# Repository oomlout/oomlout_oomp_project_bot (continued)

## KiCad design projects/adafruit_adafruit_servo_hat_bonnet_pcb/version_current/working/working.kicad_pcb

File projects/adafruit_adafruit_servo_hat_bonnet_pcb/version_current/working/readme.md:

# OOMP Project  
## Adafruit-Servo-HAT-Bonnet-PCB  by adafruit  
  
oomp key: oomp_projects_flat_adafruit_adafruit_servo_hat_bonnet_pcb  
(snippet of original readme)  
  
- Adafruit-Servo-HAT-Bonnet-PCB  
PCB files for Adafruit Servo HAT and Bonnet  
  
Format is EagleCAD schematic and board layout  
  
For more details, check out the product pages at  
  
   * http://www.adafruit.com/product/2327  
   * https://www.adafruit.com/product/3416  
  
Adafruit invests time and resources providing this open source design,   
please support Adafruit and open-source hardware by purchasing   
products from Adafruit!  
  
Designed by Adafruit Industries.    
Creative Commons Attribution, Share-Alike license, check license.txt for more information  
All text above must be included in any redistribution  
  
  full source readme at [readme_src.md](readme_src.md)  
  
source repo at: [https://github.com/adafruit/Adafruit-Servo-HAT-Bonnet-PCB](https://github.com/adafruit/Adafruit-Servo-HAT-Bonnet-PCB)  
## Board  

## Schematic  

[schematic pdf](working_schematic.pdf)  
## Images

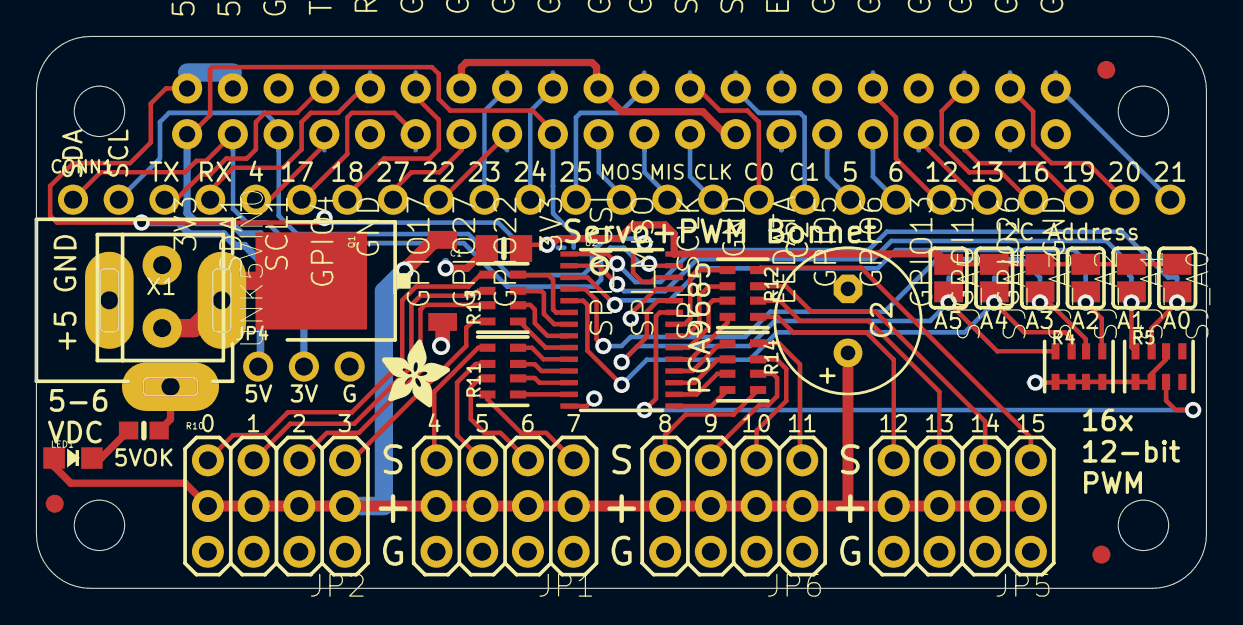
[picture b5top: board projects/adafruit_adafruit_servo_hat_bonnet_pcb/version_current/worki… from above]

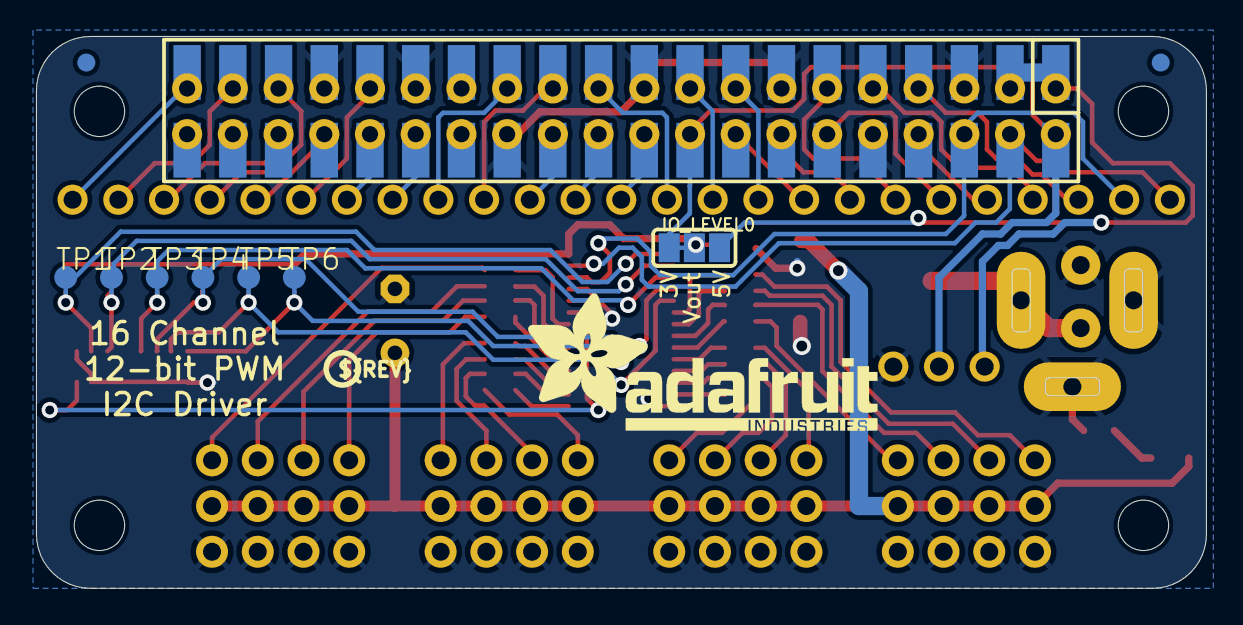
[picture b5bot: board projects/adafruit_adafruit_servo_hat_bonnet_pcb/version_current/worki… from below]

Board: 2 copper layers, 65.0 x 30.7 mm, 40 parts (9 on the bottom side), 74 nets.

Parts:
C1: 10uF; 0805-NO
C2: E3,5-8
CONN1: HEADER-1X25; 1X25_ROUND_70MIL
FID1, FID2, FID3: FIDUCIAL_1MM
IO_LEVEL0: SOLDERJUMPER_2WAY_OPEN_NOPASTE
JP1, JP2, JP5, JP6: 3X04
JP4: 1X03_ROUND
LED1: GREEN; CHIPLED_0805_NOOUTLINE
Q1: AOD417; TO252
R4, R5: 10K; RESPACK_4X0603
R10: 470; 0603-NO
R11, R12, R13, R14: 220; RESPACK_4X0603
RPI1: RASPBERRYPI_BPLUS_BONNET_THMSMT; PI_BONNET_THMSMT
SJ_A0, SJ_A1, SJ_A2, SJ_A3, SJ_A4, SJ_A5: SOLDERJUMPER_REFLOW_NOPASTE
TP1, TP2, TP3, TP4, TP5, TP6: TPB1,27; B1,27
U2: PCA9685; TSSOP28
U$6: ADAFRUIT_TEXT_20MM
U$8: ADAFRUIT_3.5MM
U$11: PCBFEAT-REV-040
UNK5VIN0: 3.5mm term; TERMBLOCK_1X2-3.5MM
X1: 2.1mm; DCJACK_2MM_PTH

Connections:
3.3V: IO_LEVEL0.1, JP4.2, RPI1.1, RPI1.17, RPI1.S1, RPI1.S17
5.0V: IO_LEVEL0.3, JP4.1, RPI1.2, RPI1.4, RPI1.S2, RPI1.S4
+5V: C2.+, JP1.2, JP1.5, JP1.8, JP1.11, JP2.2, JP2.5, JP2.8, JP2.11, JP5.2, JP5.5, JP5.8, JP5.11, JP6.2, JP6.5, JP6.8, JP6.11, LED1.A, Q1.2
A0: R5.7, SJ_A0.2, TP1.TP, U2.1
A1: R5.8, SJ_A1.2, TP2.TP, U2.2
A2: R4.5, SJ_A2.2, TP3.TP, U2.3
A3: R4.6, SJ_A3.2, TP4.TP, U2.4
A4: R4.7, SJ_A4.2, TP5.TP, U2.5
A5: R4.8, SJ_A5.2, TP6.TP, U2.24
EECLK: RPI1.28, RPI1.S28
EEDATA: RPI1.27, RPI1.S27
GND: C1.2, C2.-, JP1.3, JP1.6, JP1.9, JP1.12, JP2.3, JP2.6, JP2.9, JP2.12, JP4.3, JP5.3, JP5.6, JP5.9, JP5.12, JP6.3, JP6.6, JP6.9, JP6.12, Q1.1, R4.1, R4.2, R4.3, R4.4, R5.1, R5.2, R5.6, R10.2, RPI1.6, RPI1.9, RPI1.14, RPI1.20, RPI1.25, RPI1.30, RPI1.34, RPI1.39, RPI1.S6, RPI1.S9, RPI1.S14, RPI1.S20, RPI1.S25, RPI1.S30, RPI1.S34, RPI1.S39, U2.14, U2.25, UNK5VIN0.2, X1.GND, X1.GNDBREAK
GPIO4: CONN1.5, RPI1.7, RPI1.S7
GPIO5: CONN1.18, RPI1.29, RPI1.S29
GPIO6: CONN1.19, RPI1.31, RPI1.S31
GPIO12: CONN1.20, RPI1.32, RPI1.S32
GPIO13: CONN1.21, RPI1.33, RPI1.S33
GPIO16: CONN1.22, RPI1.36, RPI1.S36
GPIO17: CONN1.6, RPI1.11, RPI1.S11
GPIO18: CONN1.7, RPI1.12, RPI1.S12
GPIO19: CONN1.23, RPI1.35, RPI1.S35
GPIO20: CONN1.24, RPI1.38, RPI1.S38
GPIO21: CONN1.25, RPI1.40, RPI1.S40
GPIO22: CONN1.9, RPI1.15, RPI1.S15
GPIO23: CONN1.10, RPI1.16, RPI1.S16
GPIO24: CONN1.11, RPI1.18, RPI1.S18
GPIO25: CONN1.12, RPI1.22, RPI1.S22
GPIO26: RPI1.37, RPI1.S37
GPIO27: CONN1.8, RPI1.13, RPI1.S13
unnamed: LED1.C, R10.1
unnamed: JP1.4, R11.7
unnamed: JP1.1, R11.8
unnamed: JP1.7, R11.6
unnamed: JP1.10, R11.5
unnamed: JP2.1, R13.8
unnamed: JP2.4, R13.7
unnamed: JP2.7, R13.6
unnamed: JP2.10, R13.5
unnamed: JP6.10, R14.5
unnamed: JP6.7, R14.6
unnamed: JP6.4, R14.7
unnamed: JP6.1, R14.8
unnamed: JP5.10, R12.5
unnamed: JP5.7, R12.6
unnamed: JP5.4, R12.7
unnamed: JP5.1, R12.8
OE: R5.3, U2.23
PWM0: R13.4, U2.6
PWM1: R13.3, U2.7
PWM2: R13.2, U2.8
PWM3: R13.1, U2.9
PWM4: R11.4, U2.10
PWM5: R11.3, U2.11
PWM6: R11.2, U2.12
PWM7: R11.1, U2.13
PWM8: R14.4, U2.15
PWM9: R14.3, U2.16
PWM10: R14.2, U2.17
PWM11: R14.1, U2.18
PWM12: R12.4, U2.19
PWM13: R12.3, U2.20
PWM14: R12.2, U2.21
PWM15: R12.1, U2.22
PWR: Q1.3, UNK5VIN0.1, X1.PWR
RXD: CONN1.4, RPI1.10, RPI1.S10
SCL: CONN1.2, RPI1.5, RPI1.S5, U2.26
SDA: CONN1.1, RPI1.3, RPI1.S3, U2.27
SPI_CE0: CONN1.16, RPI1.24, RPI1.S24
SPI_CE1: CONN1.17, RPI1.26, RPI1.S26
SPI_MISO: CONN1.14, RPI1.21, RPI1.S21
SPI_MOSI: CONN1.13, RPI1.19, RPI1.S19
SPI_SCLK: CONN1.15, RPI1.23, RPI1.S23
TXD: CONN1.3, RPI1.8, RPI1.S8
VDDIO: C1.1, IO_LEVEL0.2, SJ_A0.1, SJ_A1.1, SJ_A2.1, SJ_A3.1, SJ_A4.1, SJ_A5.1, U2.28

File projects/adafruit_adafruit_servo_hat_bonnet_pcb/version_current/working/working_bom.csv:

"Id";"Designator";"Footprint";"Quantity";"Designation";"Supplier and ref";
1;"Q1";"TO252";1;"AOD417";;;
2;"JP5,JP2,JP1,JP6";"3X04";4;"";;;
3;"U$8";"ADAFRUIT_3.5MM";1;"";;;
4;"C1";"0805-NO";1;"10uF";;;
5;"JP4";"1X03_ROUND";1;"";;;
6;"FID3,FID2,FID1";"FIDUCIAL_1MM";3;"FIDUCIAL_1MM";;;
7;"R5,R4";"RESPACK_4X0603";2;"10K";;;
8;"U2";"TSSOP28";1;"PCA9685";;;
9;"RPI1";"PI_BONNET_THMSMT";1;"RASPBERRYPI_BPLUS_BONNET_THMSMT";;;
10;"R14,R11,R13,R12";"RESPACK_4X0603";4;"220";;;
11;"SJ_A3,SJ_A5,SJ_A4,SJ_A1,SJ_A0,SJ_A2";"SOLDERJUMPER_REFLOW_NOPASTE";6;"";;;
12;"CONN1";"1X25_ROUND_70MIL";1;"HEADER-1X25";;;
13;"C2";"E3,5-8";1;"";;;
14;"UNK5VIN0";"TERMBLOCK_1X2-3.5MM";1;"3.5mm term";;;
15;"X1";"DCJACK_2MM_PTH";1;"2.1mm";;;
16;"LED1";"CHIPLED_0805_NOOUTLINE";1;"GREEN";;;
17;"R10";"0603-NO";1;"470";;;
18;"TP5,TP2,TP1,TP3,TP4,TP6";"B1,27";6;"TPB1,27";;;
19;"U$6";"ADAFRUIT_TEXT_20MM";1;"";;;
20;"IO_LEVEL0";"SOLDERJUMPER_2WAY_OPEN_NOPASTE";1;"";;;
21;"U$11";"PCBFEAT-REV-040";1;"";;;

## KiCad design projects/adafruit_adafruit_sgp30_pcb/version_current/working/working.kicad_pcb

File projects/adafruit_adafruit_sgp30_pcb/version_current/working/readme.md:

# Adafruit-SGP30-PCB by adafruit  
This is a harvested standardized copy of a project from github.  
The original project can be found at:  
https://github.com/adafruit/Adafruit-SGP30-PCB  
Please consult that link for additional, details, files, and license information.  
Note: It was auto harvested and if the original repo had more than one board file or anything out of the ordinary the files here are likely not representative.

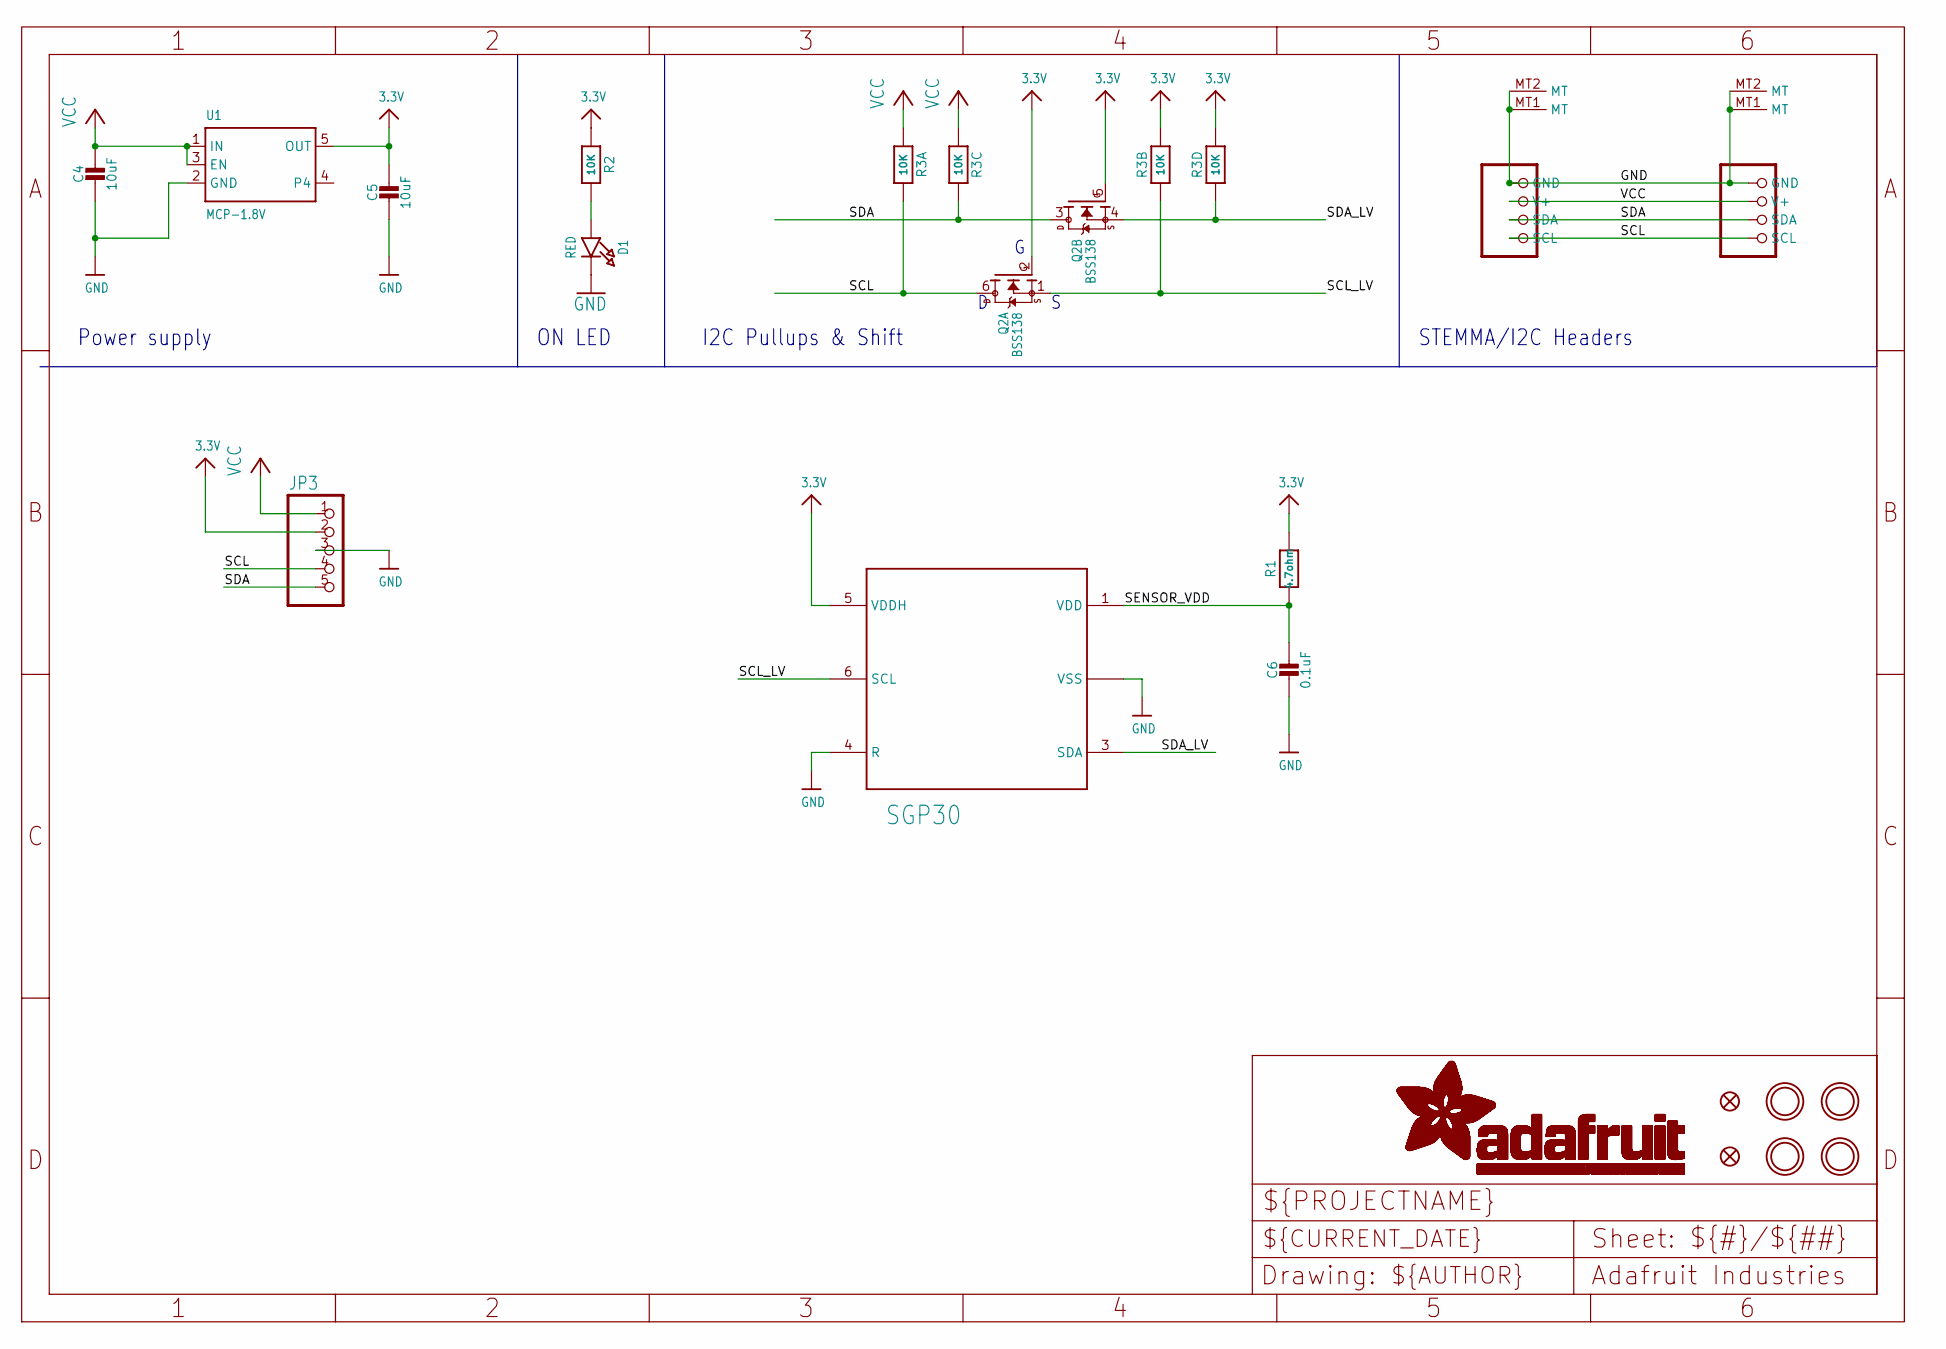
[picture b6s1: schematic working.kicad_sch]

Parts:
C4, C5: 10uF; 0805-NO
C6: 0.1uF; 0603-NO
CONN3, CONN4: STEMMA_I2C_QT; JST_SH4
D1: RED; CHIPLED_0603_NOOUTLINE
FID3, FID4: FIDUCIAL_1MM
JP3: HEADER-1X570MIL; 1X05_ROUND_70
Q2: BSS138; SOT363
R1: 4.7ohm; 0603-NO
R2: 10K; 0603-NO
R3: 10K; RESPACK_4X0603
U1: MCP-1.8V; SOT23-5
U$28, U$29, U$31, U$32: MOUNTINGHOLE2.5; MOUNTINGHOLE_2.5_PLATED
X1: SGP30

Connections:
3.3V: C5.1, JP3.2, Q2.2 (G), Q2.5 (G), R1.2, R2.1, R3.2 (1), R3.4 (1), U1.5 (OUT), X1.5 (VDDH)
GND: C4.2, C5.2, C6.2, CONN3.1 (GND), CONN3.MT1 (MT), CONN3.MT2 (MT), CONN4.1 (GND), CONN4.MT1 (MT), CONN4.MT2 (MT), D1.C, JP3.3, U1.2 (GND), X1.2 (VSS), X1.4 (R), X1.P$7 (VSS)
unnamed: D1.A, R2.2
SCL: CONN3.4 (SCL), CONN4.4 (SCL), JP3.4, Q2.6 (D), R3.8 (2)
SCL_LV: Q2.1 (S), R3.7 (2), X1.6 (SCL)
SDA: CONN3.3 (SDA), CONN4.3 (SDA), JP3.5, Q2.3 (D), R3.6 (2)
SDA_LV: Q2.4 (S), R3.5 (2), X1.3 (SDA)
SENSOR_VDD: C6.1, R1.1, X1.1 (VDD)
VCC: C4.1, CONN3.2 (V+), CONN4.2 (V+), JP3.1, R3.1, R3.3 (1), U1.1 (IN), U1.3 (EN)

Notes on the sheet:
ON LED
I2C Pullups & Shift
STEMMA/I2C Headers
Power supply

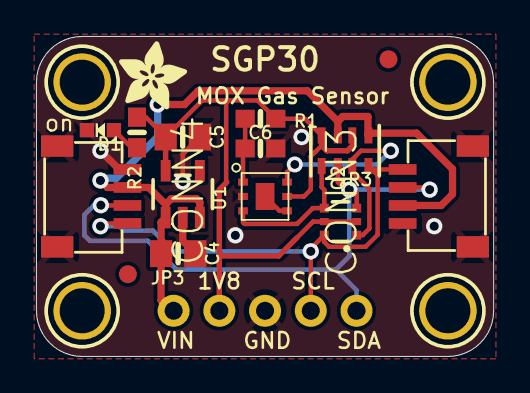
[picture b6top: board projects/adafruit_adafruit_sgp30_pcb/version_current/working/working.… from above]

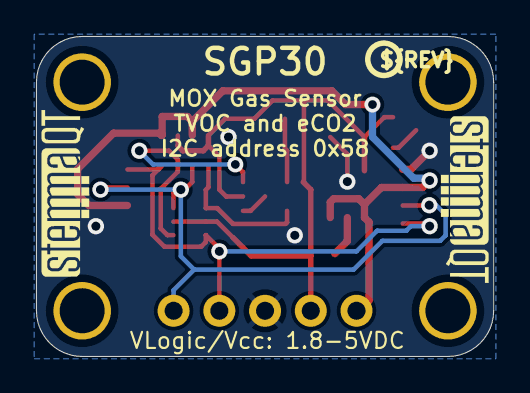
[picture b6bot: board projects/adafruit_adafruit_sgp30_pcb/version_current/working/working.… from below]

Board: 2 copper layers, 25.4 x 17.8 mm, 23 parts (3 on the bottom side), 9 nets.

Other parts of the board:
U$34: ADAFRUIT_3.5MM
U$35: PCBFEAT-REV-040
U$36, U$37: STEMMAQT

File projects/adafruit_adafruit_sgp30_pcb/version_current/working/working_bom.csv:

Row,Description,Part,References,Value,Footprint,Quantity Per PCB,Status,Datasheet
1,,CAP_CERAMIC0603_NO,C6,0.1uF,0603-NO,1, ,
2,,CAP_CERAMIC0805-NOOUTLINE,C4 C5,10uF,0805-NO,2, ,
3,,STEMMA_I2C_QT,CONN3 CONN4,STEMMA_I2C_QT,JST_SH4,2, ,
4,,LED0603_NOOUTLINE,D1,RED,CHIPLED_0603_NOOUTLINE,1, ,
5,,HEADER-1X570MIL,JP3,HEADER-1X570MIL,1X05_ROUND_70,1, ,
6,,MOSFET-N_DUAL,Q2,BSS138,SOT363,1, ,
7,,RESISTOR_0603_NOOUT,R1,4.7ohm,0603-NO,1, ,
8,,RESISTOR_0603_NOOUT,R2,10K,0603-NO,1, ,
9,,RESISTOR_4PACK,R3,10K,RESPACK_4X0603,1, ,
10,,VREG_SOT23-5,U1,MCP-1.8V,SOT23-5,1, ,
11,,SGP30,X1,SGP30,SGP30,1, ,





Project info:
Schematic:,working
Variant:,default
Revision:,
Date:,2023-08-03_17-21-23
KiCad Version:,7.0.6-7.0.6~ubuntu22.04.1
Statistics:
Component Groups:,11
Component Count:,13 (0 SMD/ 0 THT)
Fitted Components:,13 (0 SMD/ 0 THT)
Number of PCBs:,1
Total Components:,13

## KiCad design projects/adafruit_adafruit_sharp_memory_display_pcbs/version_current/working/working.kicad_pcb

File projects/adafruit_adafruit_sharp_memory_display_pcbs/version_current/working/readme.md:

# OOMP Project  
## Adafruit-Sharp-Memory-Display-PCBs  by adafruit  
  
oomp key: oomp_projects_flat_adafruit_adafruit_sharp_memory_display_pcbs  
(snippet of original readme)  
  
- PCB for the Adafruit Sharp Memory display breakout board  
  
<br />  

[The 96x96 resolution SHARP Memory LCD is no longer made, but we have a higher-resolution 168x144 display available in the shop](https://www.adafruit.com/product/3502).  
  
The 1.3" and 2.7" SHARP Memory LCD displays are a cross between an eInk (e-paper) display and an LCD. They have the ultra-low power usage of eInk and the fast-refresh rates of an LCD. This model has a matt silver background, and pixels show up as little mirrors for a silver-reflective display, a really beautiful and unique look. It does not have a backlight, but it is daylight readable. For dark/night reading you may need to illuminate the LCD area with external LEDs.  
  
The display is 3V powered and 3V logic, so we placed it on a fully assembled & tested breakout board with a 3V regulator and level shifting circuitry. The display slots into a ZIF socket on board and we use a piece of double-sided tape to adhere it onto one side. There are four mounting holes so you can easily attach it to a box.  
  
The display is 'write only' which means that it only needs 3 pins to send data. However, the downside of a write-only display is that the entire 96x96 bits (1,152 bytes) must be buffered by the microcontroller driver. On an Arduino Uno/Leonardo that  
  full source readme at [readme_src.md](readme_src.md)  
  
source repo at: [https://github.com/adafruit/Adafruit-Sharp-Memory-Display-PCBs](https://github.com/adafruit/Adafruit-Sharp-Memory-Display-PCBs)  
## Board  

## Schematic  

[schematic pdf](working_schematic.pdf)  
## Images

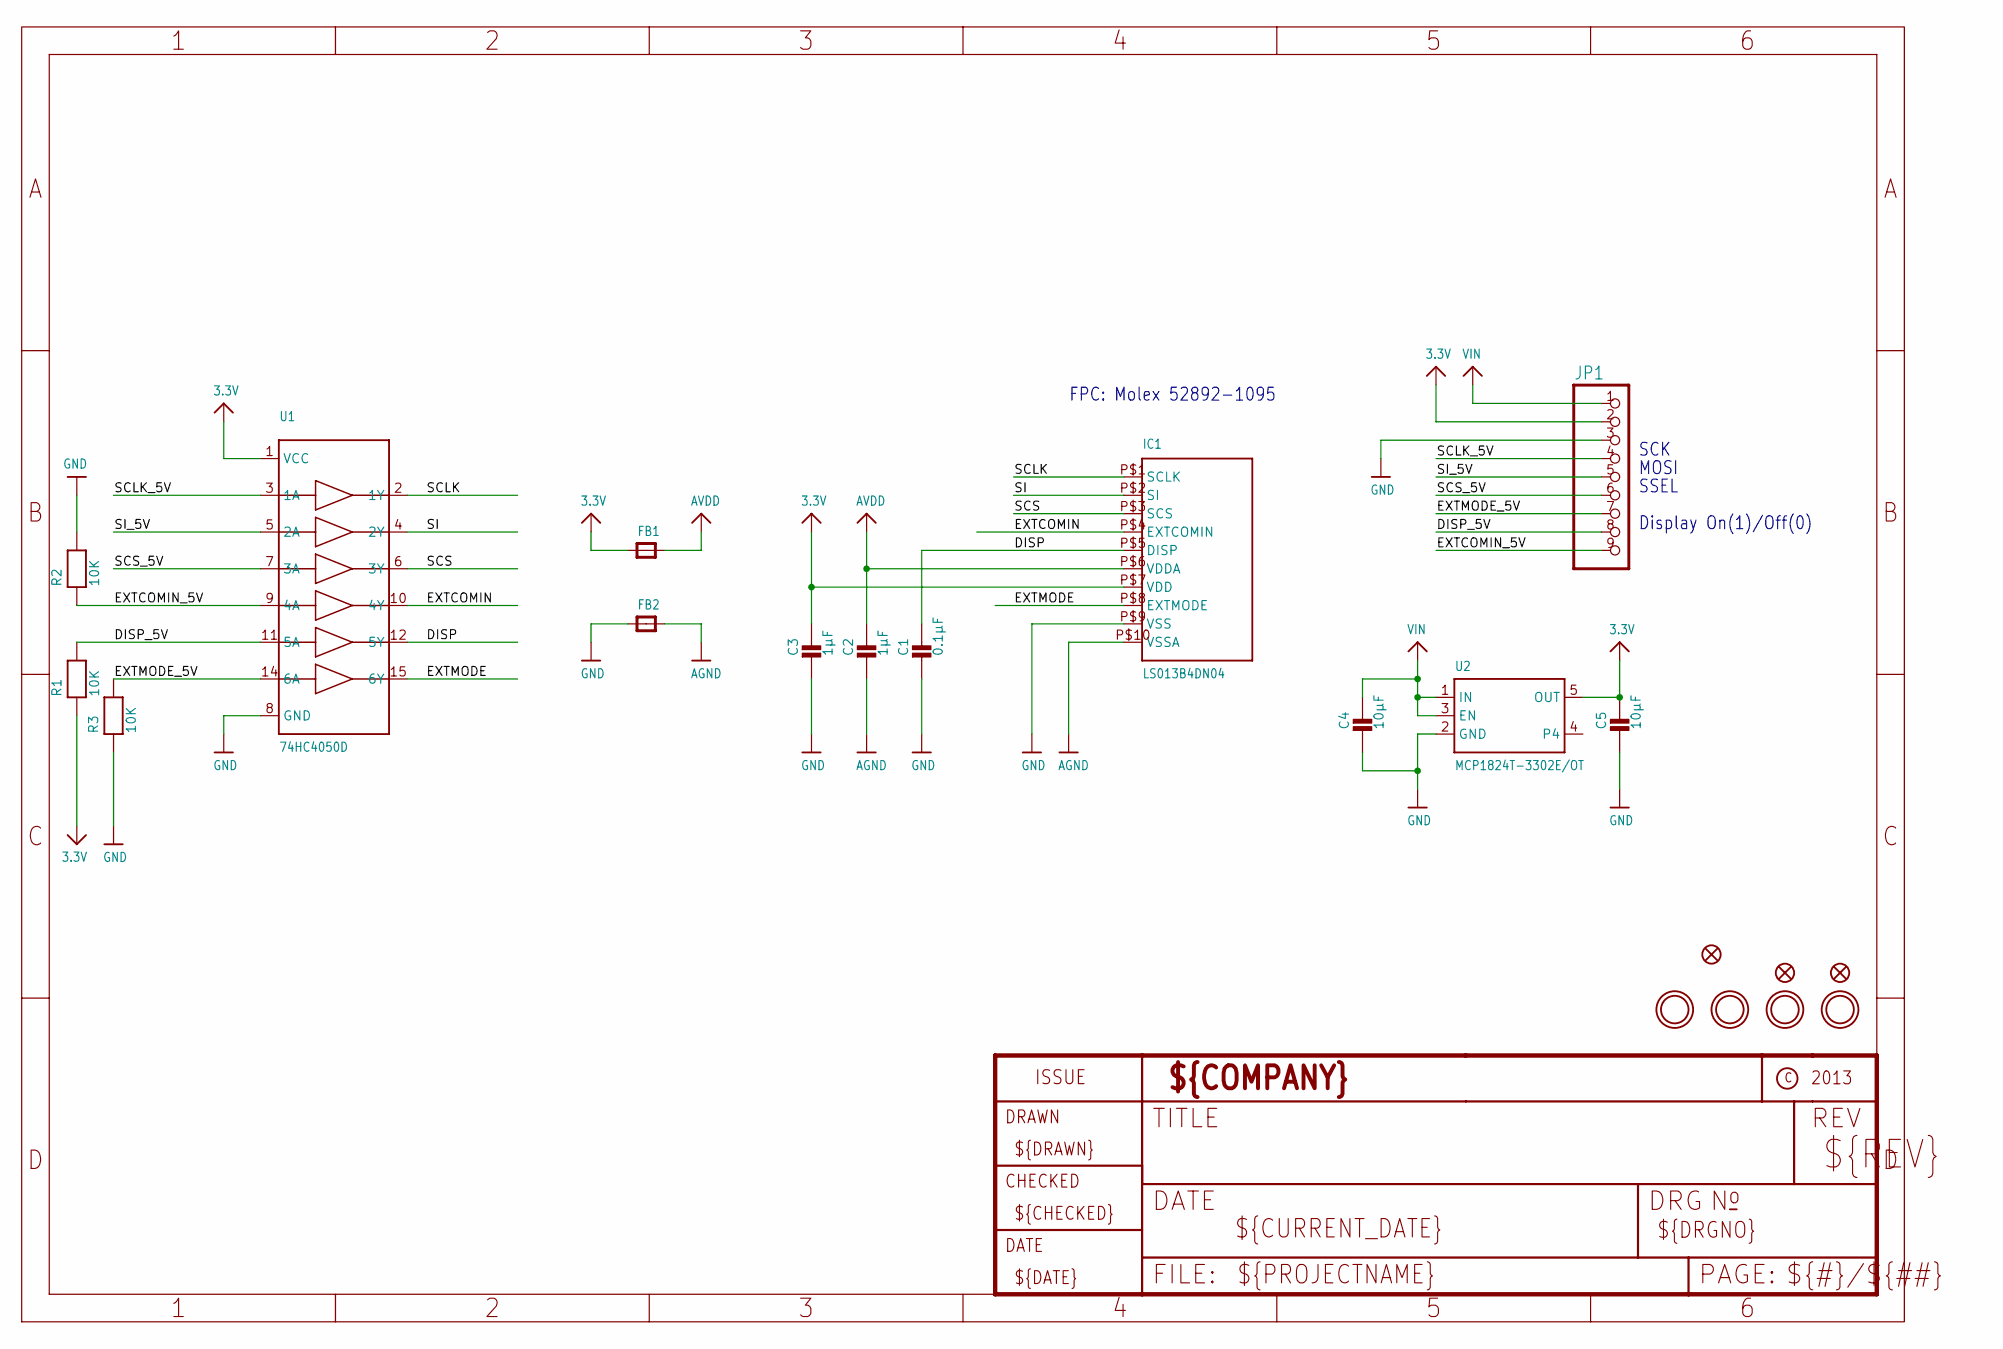
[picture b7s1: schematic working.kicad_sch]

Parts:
C1: 0.1µF; _0805
C2, C3: 1µF; _0805
C4, C5: 10µF; _0805
FB1, FB2: FERRITE_0805; _0805
FID1, FID2, FID3: FIDUCIAL""; FIDUCIAL_1MM
IC1: LS013B4DN04; FPC_10PIN_52892-1095
JP1: HEADER-1X970MIL; 1X09_ROUND_70
R1, R2, R3: 10K; _0805
U1: 74HC4050D; SOIC16
U2: MCP1824T-3302E/OT; SOT23-5
U$21, U$22, U$27, U$28: MOUNTINGHOLE3.0THIN; MOUNTINGHOLE_3.0_PLATEDTHIN

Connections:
3.3V: C3.1, C5.1, FB1.1, IC1.P$7 (VDD), JP1.2, R1.1, U1.1 (VCC), U2.5 (OUT)
AGND: C2.2, FB2.2, IC1.P$10 (VSSA)
AVDD: C2.1, FB1.2, IC1.P$6 (VDDA)
DISP: C1.1, IC1.P$5 (DISP), U1.12 (5Y)
DISP_5V: JP1.8, R1.2, U1.11 (5A)
EXTCOMIN: IC1.P$4 (EXTCOMIN), U1.10 (4Y)
EXTCOMIN_5V: JP1.9, R2.1, U1.9 (4A)
EXTMODE: IC1.P$8 (EXTMODE), U1.15 (6Y)
EXTMODE_5V: JP1.7, R3.2, U1.14 (6A)
GND: C1.2, C3.2, C4.2, C5.2, FB2.1, IC1.P$9 (VSS), JP1.3, R2.2, R3.1, U1.8 (GND), U2.2 (GND)
SCLK: IC1.P$1 (SCLK), U1.2 (1Y)
SCLK_5V: JP1.4, U1.3 (1A)
SCS: IC1.P$3 (SCS), U1.6 (3Y)
SCS_5V: JP1.6, U1.7 (3A)
SI: IC1.P$2 (SI), U1.4 (2Y)
SI_5V: JP1.5, U1.5 (2A)
VIN: C4.1, JP1.1, U2.1 (IN), U2.3 (EN)

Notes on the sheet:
SSEL
SCK
FPC: Molex 52892-1095
Display On(1)/Off(0)
MOSI

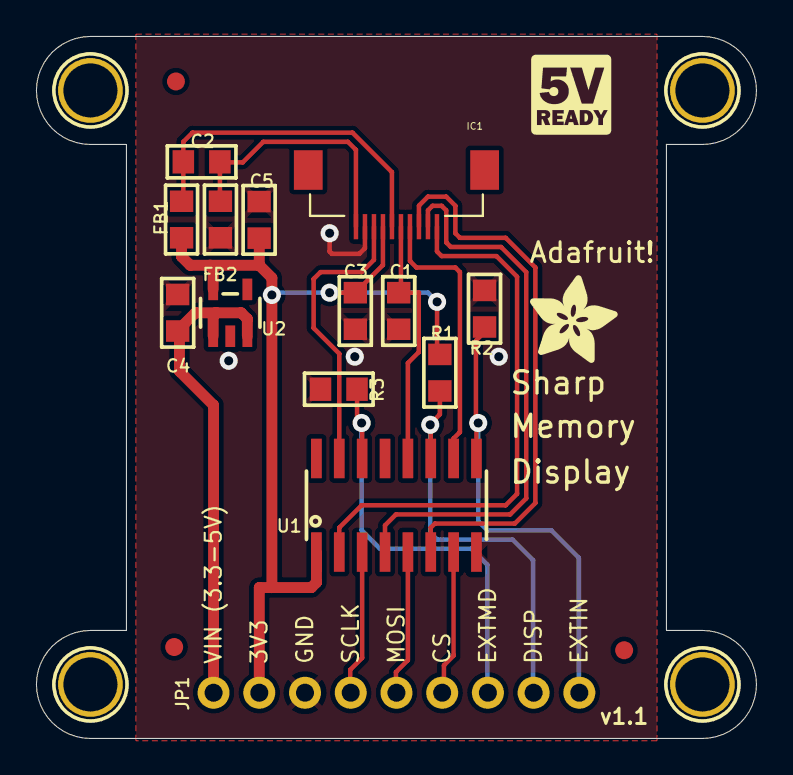
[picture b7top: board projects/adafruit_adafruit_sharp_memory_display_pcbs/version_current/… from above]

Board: 16 copper layers, 40.0 x 39.0 mm, 23 parts (0 on the bottom side), 17 nets.

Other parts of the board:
U$19: LOGIC_5VREADY_5MM
U$29: ADAFRUIT_5MM
